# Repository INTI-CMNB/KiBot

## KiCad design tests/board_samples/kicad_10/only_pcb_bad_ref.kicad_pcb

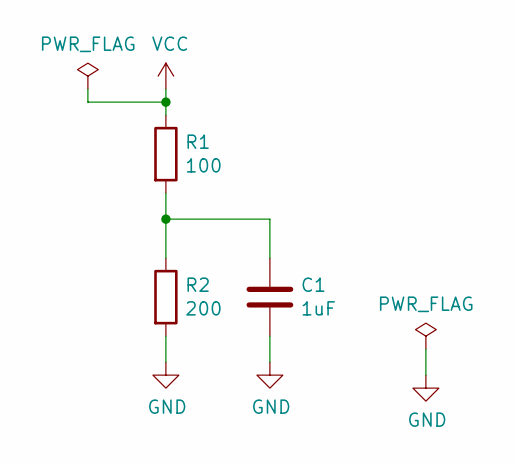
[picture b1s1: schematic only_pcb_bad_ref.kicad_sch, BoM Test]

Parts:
C1: 1uF; C_0805_2012Metric
R1: 100; R_0805_2012Metric
R2: 200; R_0805_2012Metric

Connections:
GND: C1.2, R2.2
unnamed: C1.1, R1.2, R2.1
VCC: R1.1

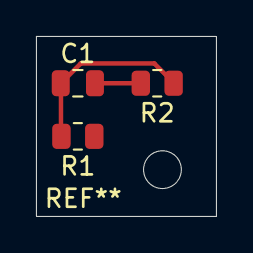
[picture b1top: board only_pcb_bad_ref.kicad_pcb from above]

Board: 2 copper layers, 10.0 x 10.0 mm, 3 parts (0 on the bottom side), 2 nets.
